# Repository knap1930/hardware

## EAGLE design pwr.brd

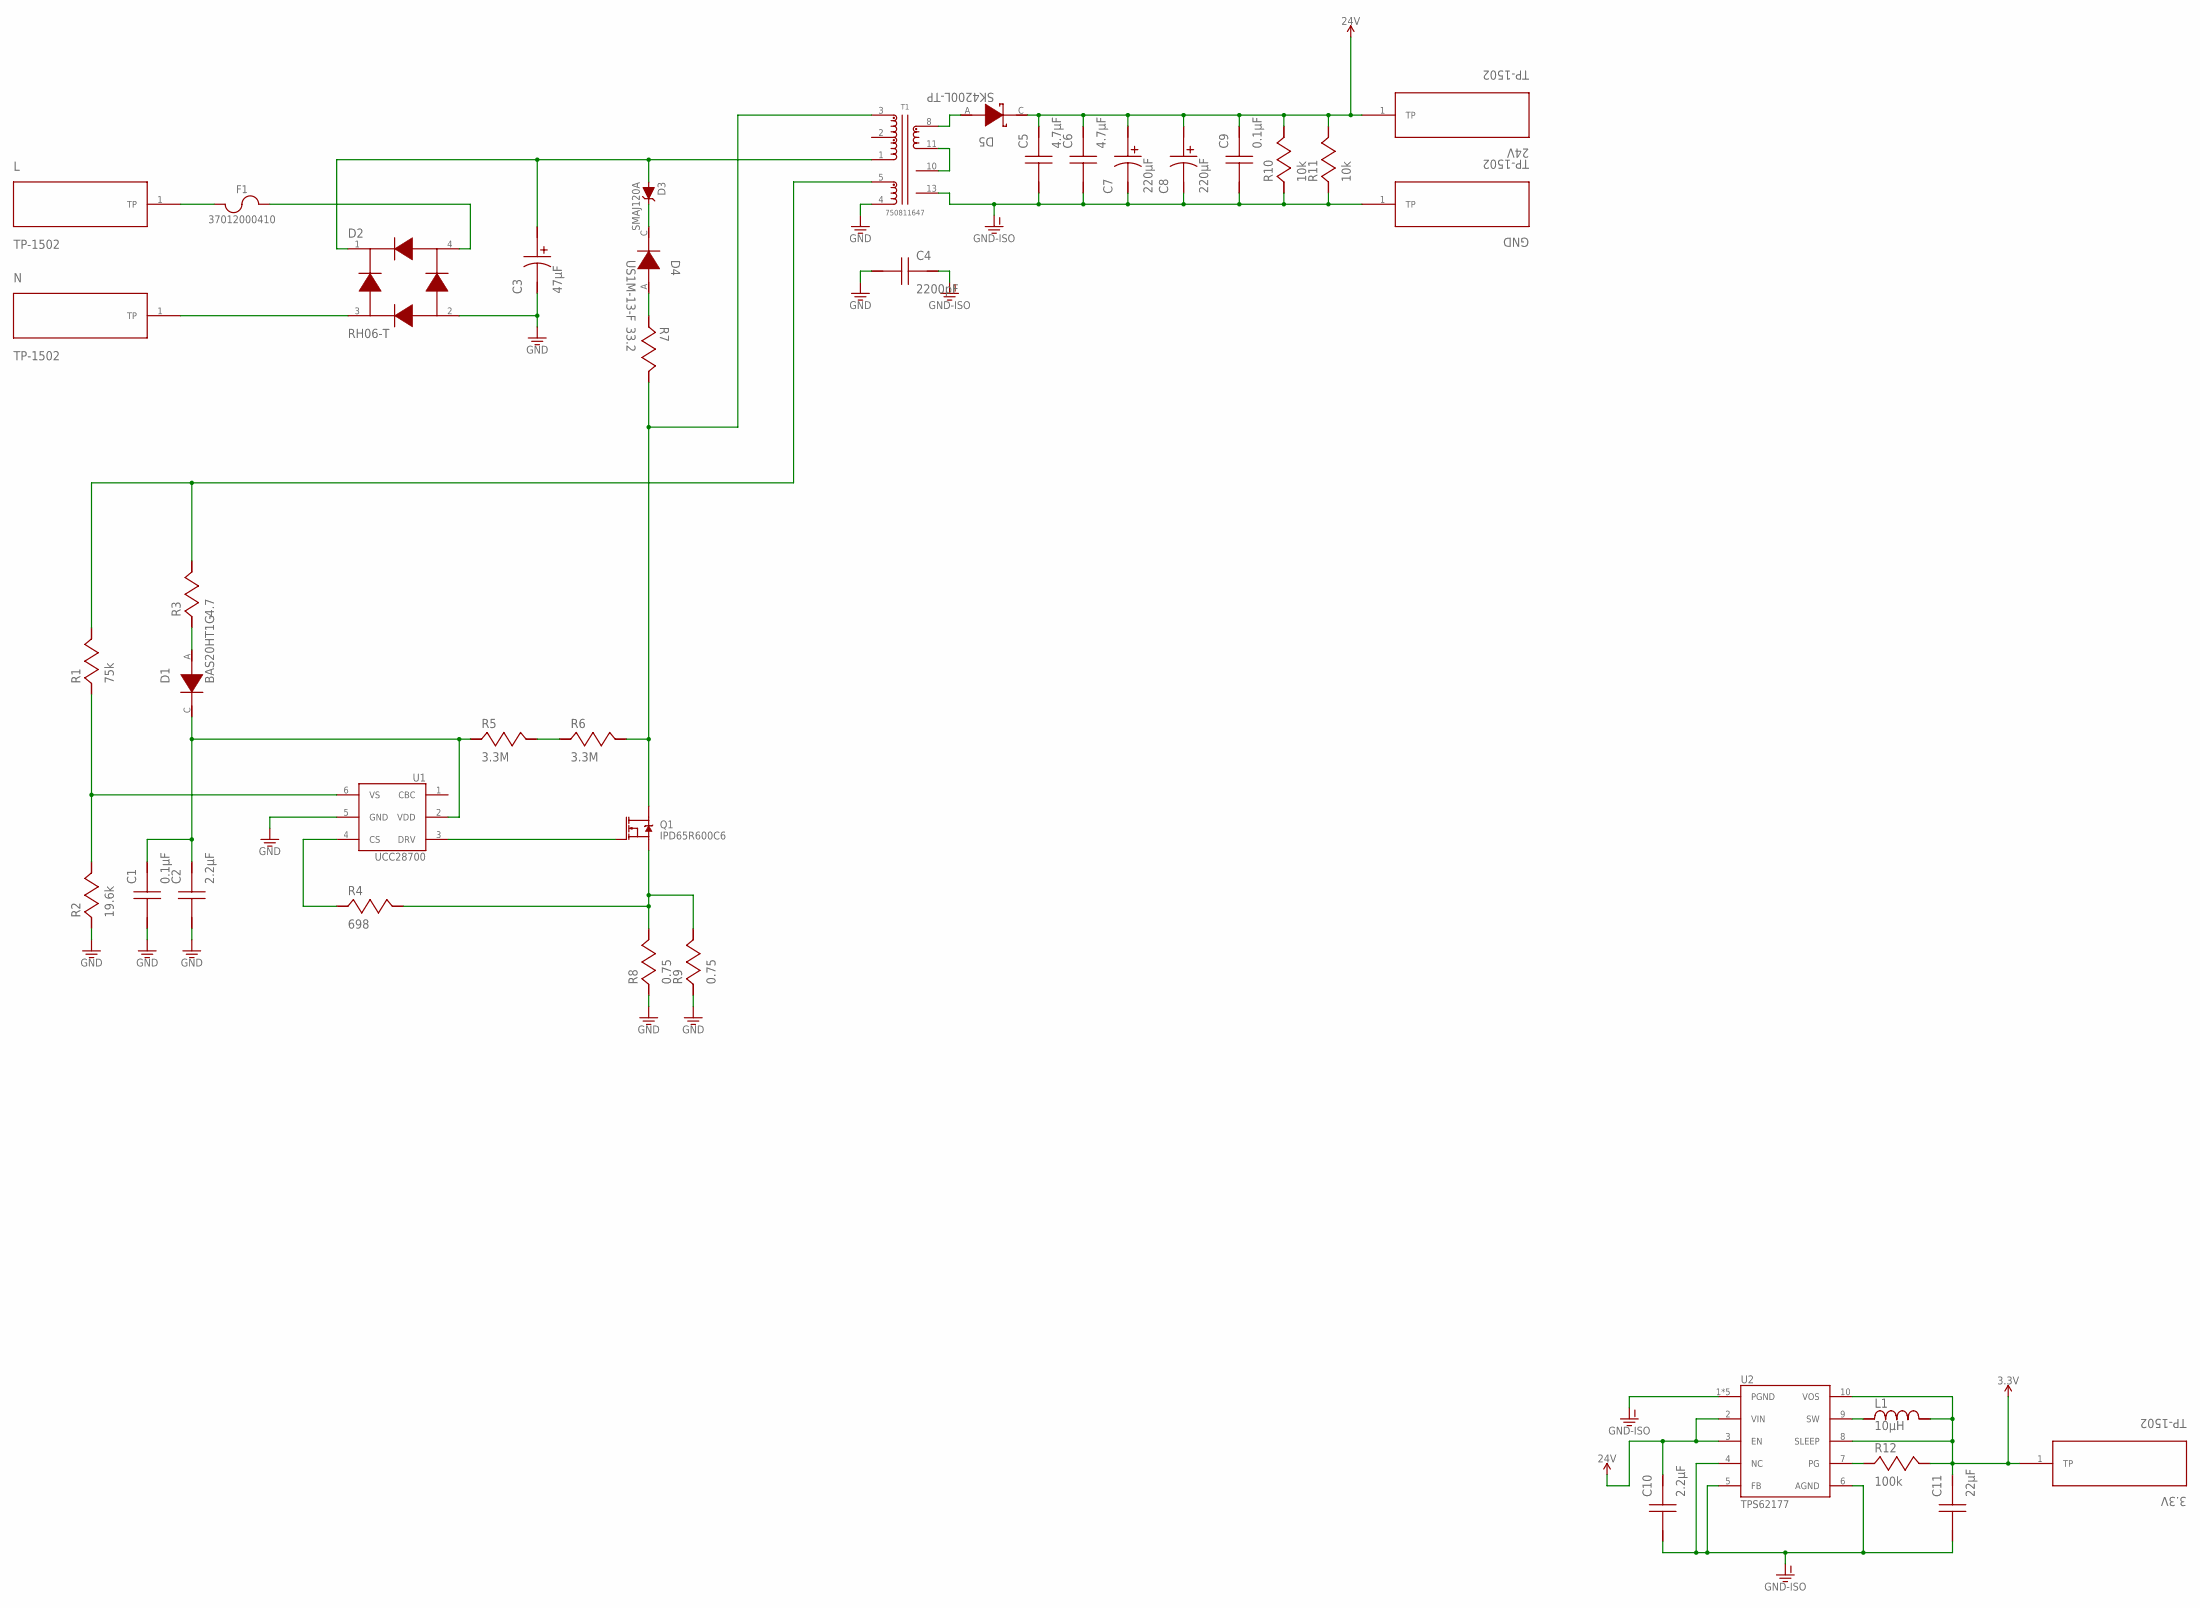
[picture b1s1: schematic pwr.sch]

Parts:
3.3V, 24V: TP-1502
C1: 0.1µF; 0603
C2: 2.2µF; 1206
C3: 47µF; CAPPR7.5-18X20
C4: 2200pF; DE1E3KX222MA4BL01
C5, C6: 4.7µF; 1206
C7, C8: 220µF; CAPPR5-10X16
C9: 0.1µF; 0805
C10: 2.2µF; 0603
C11: 22µF; 0805
D1: BAS20HT1G; SOD-323
D2: RH06-T; MINIDIP
D3: SMAJ120A; SMA
D4: US1M-13-F; SMA
D5: SK4200L-TP; SMC
F1: 37012000410; TR5_FUSE_8.5
GND: TP-1502
L: TP-1502
L1: 10µH; SDR0503
N: TP-1502
Q1: IPD65R600C6; TO-252
R1: 75k; 0603
R2: 19.6k; 0603
R3: 4.7; 1206
R4: 698; 1206
R5, R6: 3.3M; 0805
R7: 33.2; 1210
R8, R9: 0.75; 1206
R10, R11: 10k; 1206
R12: 100k; 0402
T1: 750811647
U1: UCC28700; SOT-23(6)
U2: TPS62177; P-WSON(10)

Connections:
3.3V: 3.3V.1, C11.1, L1.2, R12.1, U2.8 (SLEEP), U2.10 (VOS)
24V: 24V.1, C5.1, C6.1, C7.P$1 (1), C8.P$1 (1), C9.1, C10.1, D5.C, R10.1, R11.1, U2.2 (VIN), U2.3 (EN)
GND: C1.2, C2.2, C3.P$2 (2), C4.2, D2.2, R2.2, R8.2, R9.2, T1.4, U1.5 (GND)
GND-ISO: C4.1, C5.2, C6.2, C7.P$2 (2), C8.P$2 (2), C9.2, C10.2, C11.2, GND.1, R10.2, R11.2, T1.13, U2.1 (PGND), U2.4 (NC), U2.5 (FB), U2.6 (AGND), U2.GND, U2.P$1 (PGND), U2.P$2 (PGND), U2.P$10 (PGND)
unnamed: D2.4, F1.2
unnamed: D2.3, N.1
unnamed: C3.P$1 (1), D2.1, D3.A, T1.1
unnamed: R12.2, U2.7 (PG)
unnamed: L1.1, U2.9 (SW)
unnamed: D5.A, T1.8
unnamed: T1.10, T1.11
unnamed: D3.C, D4.C
unnamed: D4.A, R7.2
unnamed: Q1.2 (D), R6.1, R7.1, T1.3
unnamed: F1.1, L.1
unnamed: Q1.1 (G), U1.3 (DRV)
unnamed: C1.1, C2.1, D1.C, R5.2, U1.2 (VDD)
unnamed: Q1.3 (S), R4.1, R8.1, R9.1
unnamed: D1.A, R3.2
unnamed: R1.1, R3.1, T1.5
unnamed: R4.2, U1.4 (CS)
unnamed: R5.1, R6.2
unnamed: R1.2, R2.1, U1.6 (VS)

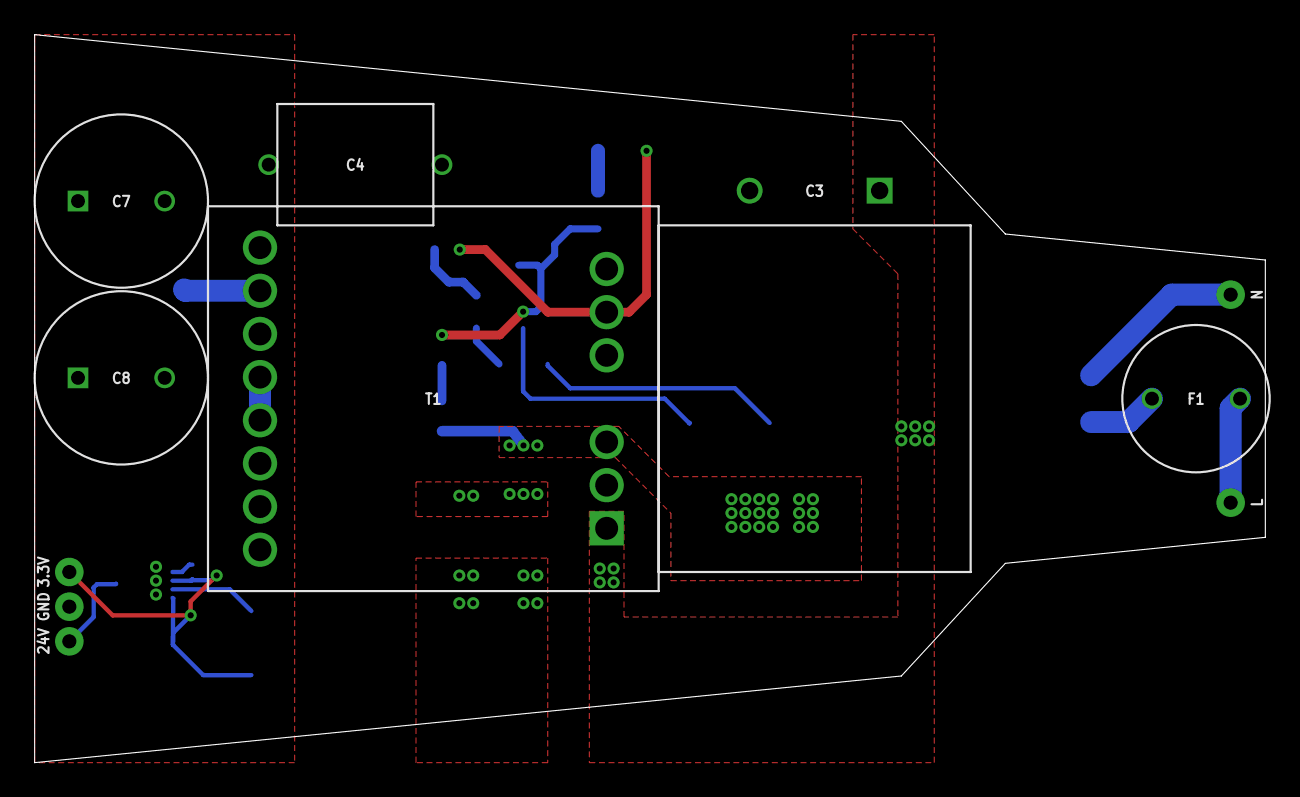
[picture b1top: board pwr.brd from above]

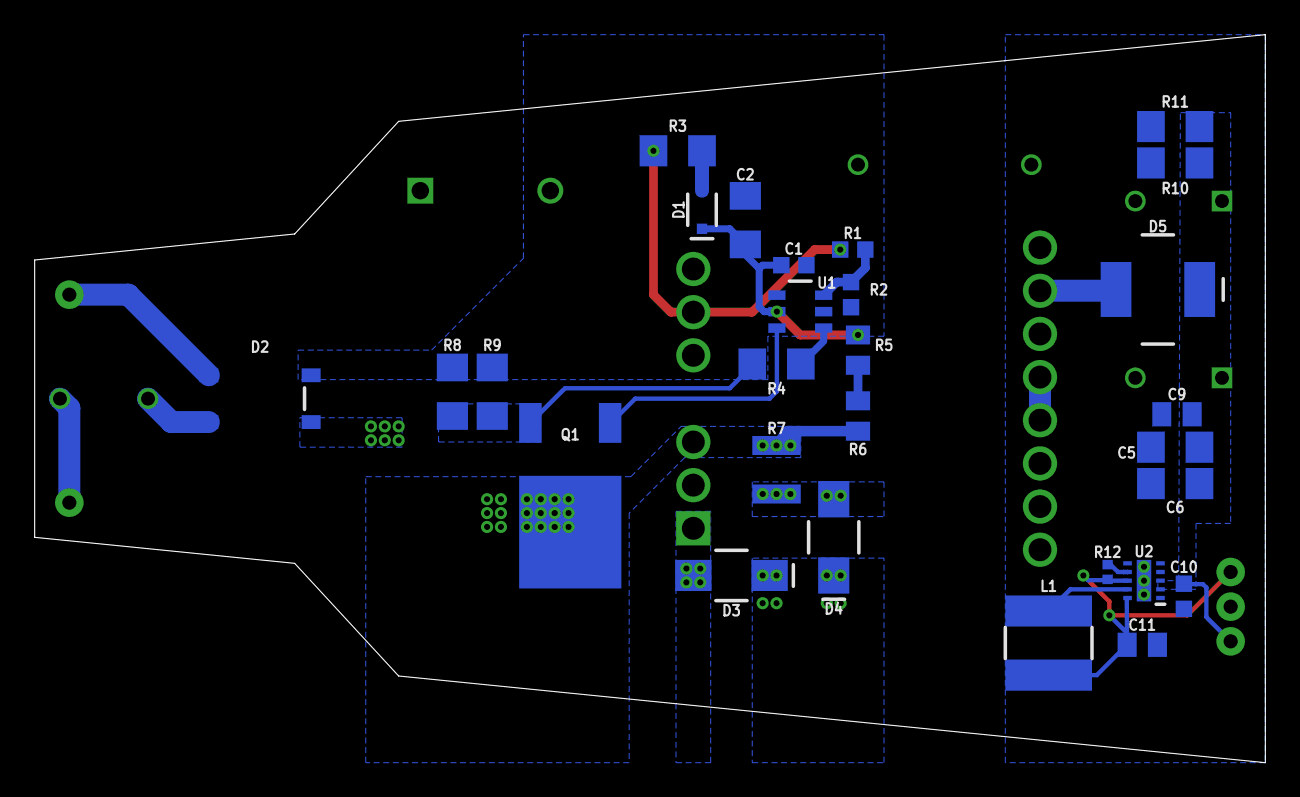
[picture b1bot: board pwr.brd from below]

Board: 2 copper layers, 71.0 x 42.0 mm, 39 parts (28 on the bottom side), 23 nets.

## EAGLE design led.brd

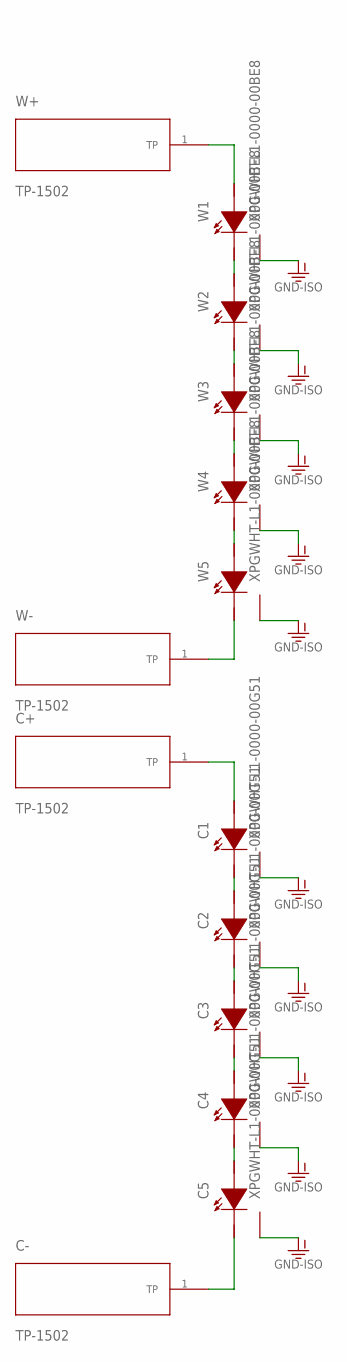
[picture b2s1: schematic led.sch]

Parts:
C1, C2, C3, C4, C5: XPGWHT-L1-0000-00G51; XLAMP-XPG
C+: TP-1502
C-: TP-1502
W1, W2, W3, W4, W5: XPGWHT-L1-0000-00BE8; XLAMP-XPG
W+: TP-1502
W-: TP-1502

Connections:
GND-ISO: C1.GND, C1.P$1 (GND), C1.P$2 (GND), C1.P$3 (GND), C2.GND, C2.P$1 (GND), C2.P$2 (GND), C2.P$3 (GND), C3.GND, C3.P$1 (GND), C3.P$2 (GND), C3.P$3 (GND), C4.GND, C4.P$1 (GND), C4.P$2 (GND), C4.P$3 (GND), C5.GND, C5.P$1 (GND), C5.P$2 (GND), C5.P$3 (GND), W1.GND, W1.P$1 (GND), W1.P$2 (GND), W1.P$3 (GND), W2.GND, W2.P$1 (GND), W2.P$2 (GND), W2.P$3 (GND), W3.GND, W3.P$1 (GND), W3.P$2 (GND), W3.P$3 (GND), W4.GND, W4.P$1 (GND), W4.P$2 (GND), W4.P$3 (GND), W5.GND, W5.P$1 (GND), W5.P$2 (GND), W5.P$3 (GND)
unnamed: C2.C, C3.A
unnamed: C1.C, C2.A
unnamed: C1.A, C+.1
unnamed: C5.C, C-.1
unnamed: W4.C, W5.A
unnamed: W1.C, W2.A
unnamed: W2.C, W3.A
unnamed: W3.C, W4.A
unnamed: C3.C, C4.A
unnamed: C4.C, C5.A
unnamed: W1.A, W+.1
unnamed: W5.C, W-.1

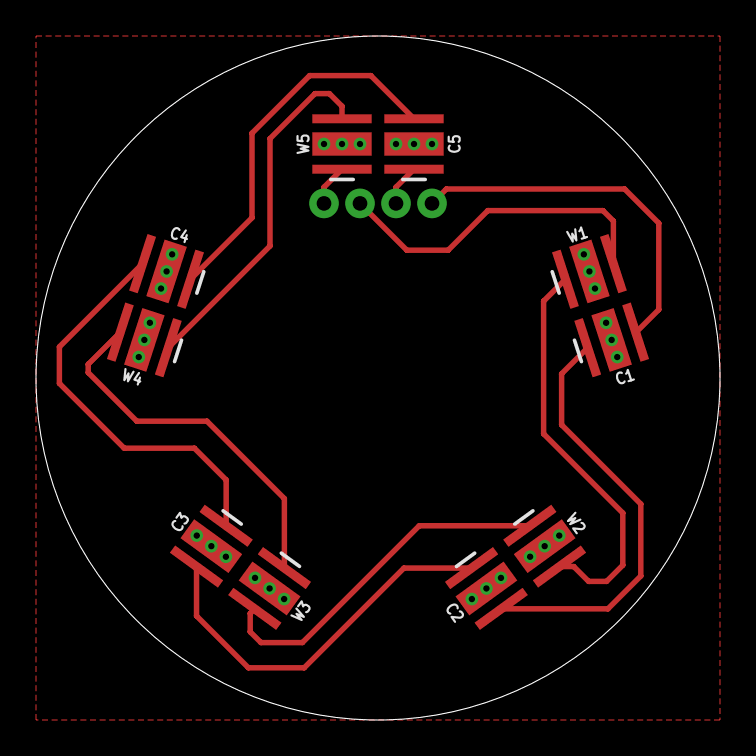
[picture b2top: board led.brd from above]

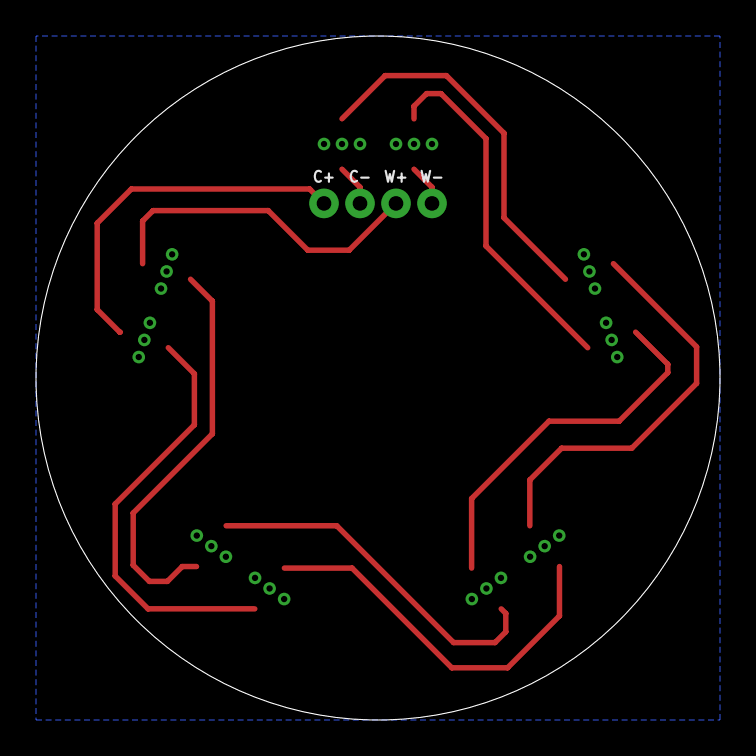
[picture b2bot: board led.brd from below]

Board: 2 copper layers, 38.0 x 38.0 mm, 14 parts (4 on the bottom side), 13 nets.

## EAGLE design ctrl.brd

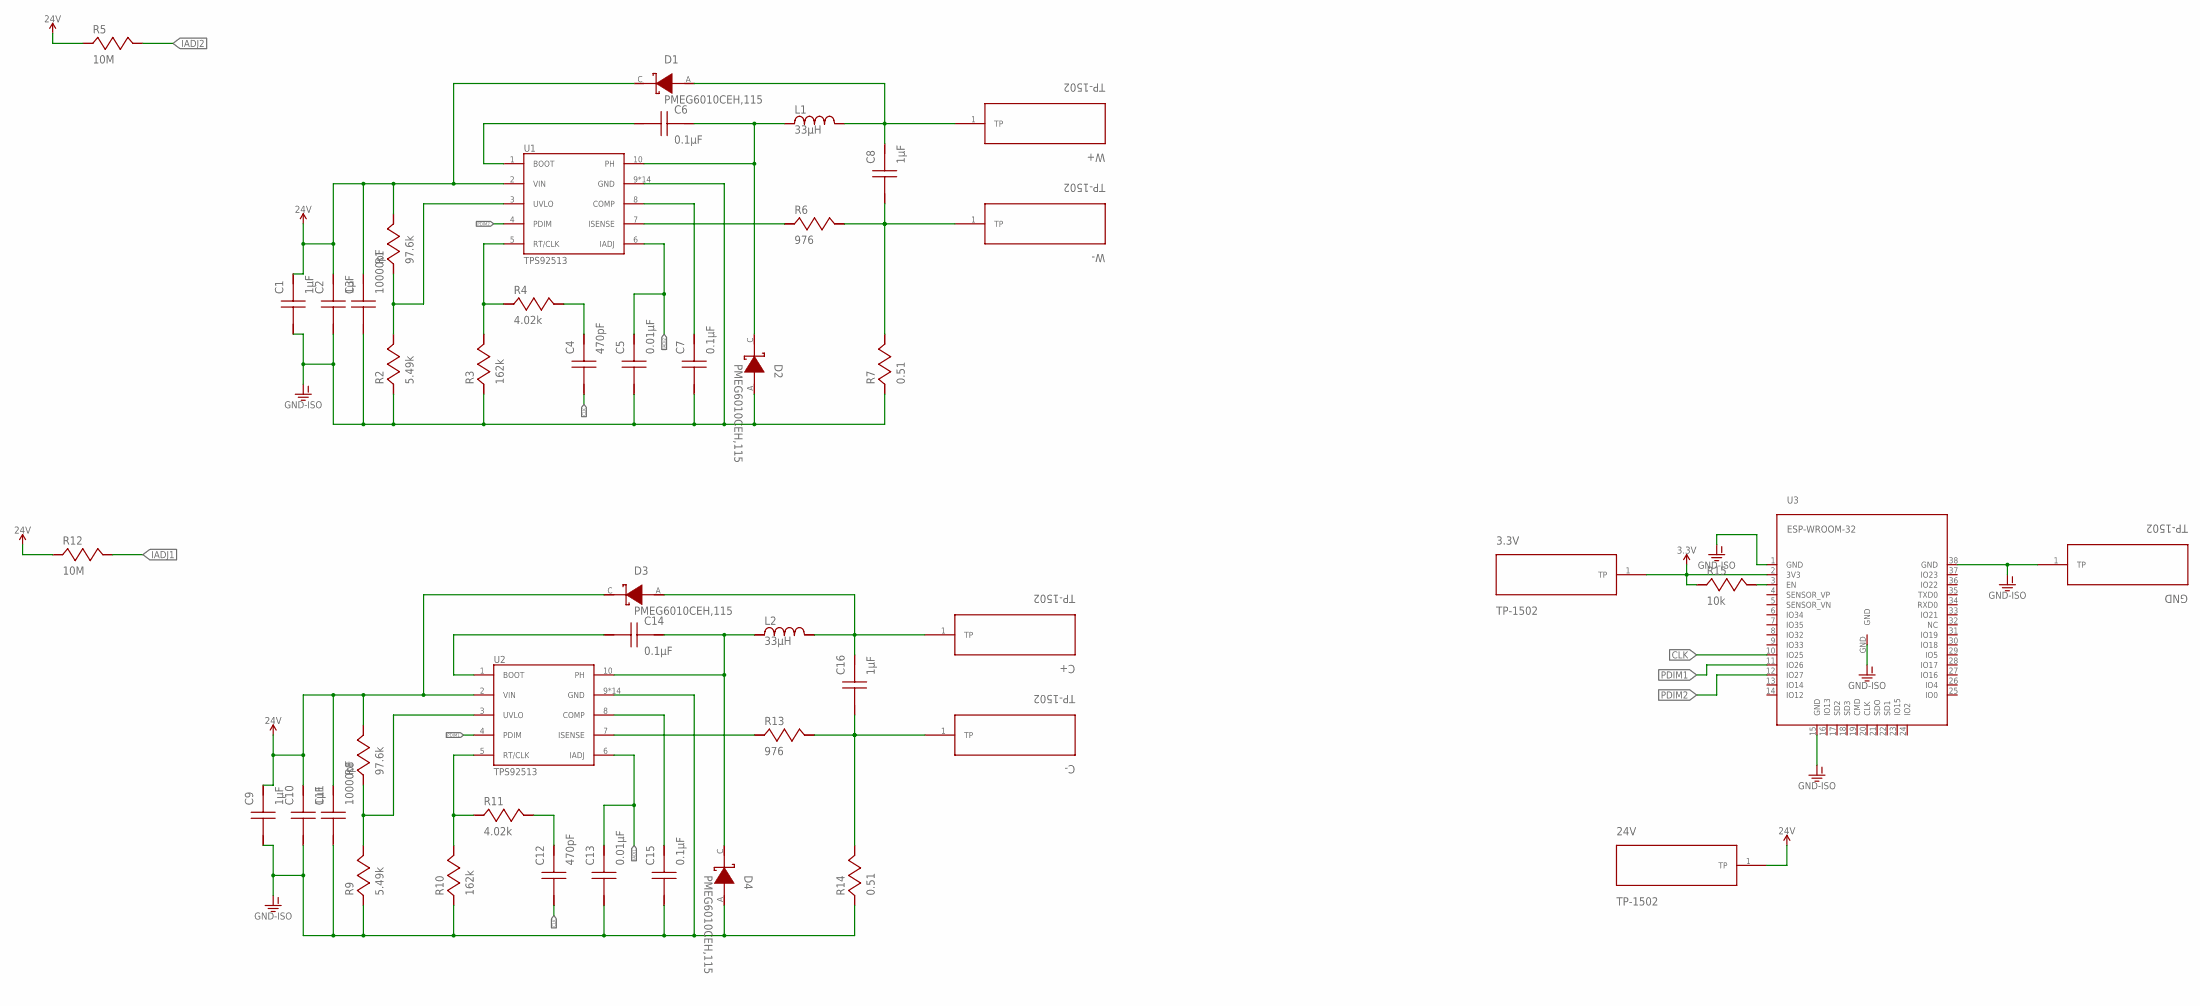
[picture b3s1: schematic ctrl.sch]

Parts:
3.3V, 24V: TP-1502
C1, C2, C9, C10: 1µF; 1206
C3, C11: 10000pF; 0402
C4, C12: 470pF; 0603
C5, C13: 0.01μF; 0805
C6, C14: 0.1µF; 0603
C7, C15: 0.1µF; 0805
C8, C16: 1µF; 0805
C+: TP-1502
C-: TP-1502
D1, D2, D3, D4: PMEG6010CEH,115; SOD-123F
GND: TP-1502
L1, L2: 33µH; SRN6045
R1, R8: 97.6k; 0402
R2, R9: 5.49k; 0402
R3, R10: 162k; 0402
R4, R11: 4.02k; 0603
R5, R12: 10M; 0402
R6, R13: 976; 0402
R7, R14: 0.51; 0805
R15: 10k; 0603
U1, U2: TPS92513
U3: ESP-WROOM-32
W+: TP-1502
W-: TP-1502

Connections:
3.3V: 3.3V.1, R15.2, U3.2 (3V3)
24V: 24V.1, C1.1, C2.1, C3.1, C9.1, C10.1, C11.1, D1.C, D3.C, R1.1, R5.2, R8.1, R12.2, U1.2 (VIN), U2.2 (VIN)
CLK: C4.2, C12.2, U3.10 (IO25)
GND-ISO: C1.2, C2.2, C3.2, C5.2, C7.2, C9.2, C10.2, C11.2, C13.2, C15.2, D2.A, D4.A, GND.1, R2.2, R3.2, R7.2, R9.2, R10.2, R14.2, U1.9 (GND), U1.GND-ISO (GND), U1.P$1 (GND), U1.P$2 (GND), U1.P$3 (GND), U1.P$4 (GND), U1.P$5 (GND), U1.P$6 (GND), U1.P$7 (GND), U1.P$8 (GND), U1.P$9 (GND), U1.P$10 (GND), U1.P$11 (GND), U1.P$12 (GND), U2.9 (GND), U2.GND-ISO (GND), U2.P$1 (GND), U2.P$2 (GND), U2.P$3 (GND), U2.P$4 (GND), U2.P$5 (GND), U2.P$6 (GND), U2.P$7 (GND), U2.P$8 (GND), U2.P$9 (GND), U2.P$10 (GND), U2.P$11 (GND), U2.P$12 (GND), U3.1 (GND), U3.15 (GND), U3.38 (GND), U3.GND
IADJ1: C13.1, R12.1, U2.6 (IADJ)
IADJ2: C5.1, R5.1, U1.6 (IADJ)
unnamed: R1.2, R2.1, U1.3 (UVLO)
unnamed: R8.2, R9.1, U2.3 (UVLO)
unnamed: C14.1, D4.C, L2.1, U2.10 (PH)
unnamed: R10.1, R11.2, U2.5 (RT/CLK)
unnamed: C15.1, U2.8 (COMP)
unnamed: C14.2, U2.1 (BOOT)
unnamed: R13.2, U2.7 (ISENSE)
unnamed: C12.1, R11.1
unnamed: C16.1, C+.1, D3.A, L2.2
unnamed: C16.2, C-.1, R13.1, R14.1
unnamed: C6.1, D2.C, L1.1, U1.10 (PH)
unnamed: R3.1, R4.2, U1.5 (RT/CLK)
unnamed: C7.1, U1.8 (COMP)
unnamed: C6.2, U1.1 (BOOT)
unnamed: R6.2, U1.7 (ISENSE)
unnamed: C8.1, D1.A, L1.2, W+.1
unnamed: C4.1, R4.1
unnamed: C8.2, R6.1, R7.1, W-.1
unnamed: R15.1, U3.3 (EN)
PDIM1: U2.4 (PDIM), U3.11 (IO26)
PDIM2: U1.4 (PDIM), U3.12 (IO27)

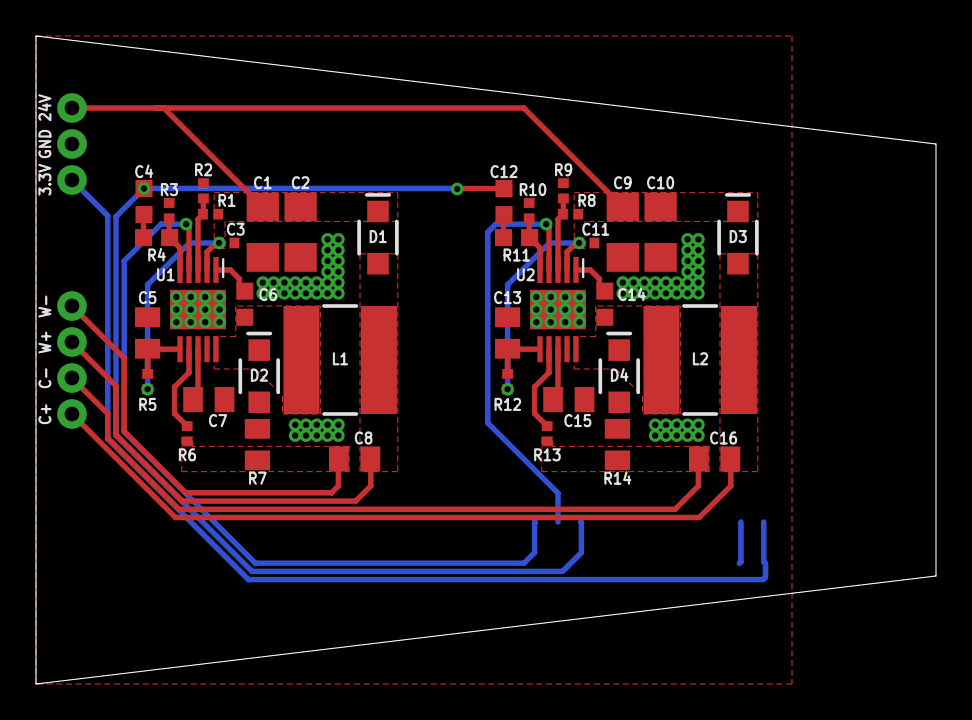
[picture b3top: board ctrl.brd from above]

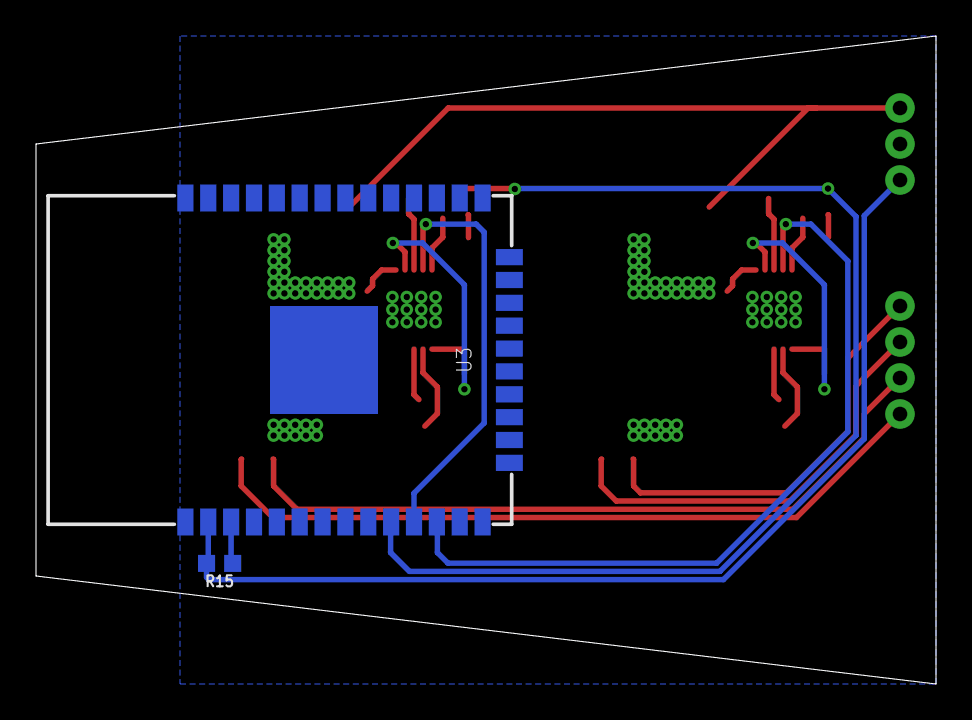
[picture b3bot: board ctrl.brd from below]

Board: 2 copper layers, 50.0 x 36.0 mm, 47 parts (2 on the bottom side), 27 nets.

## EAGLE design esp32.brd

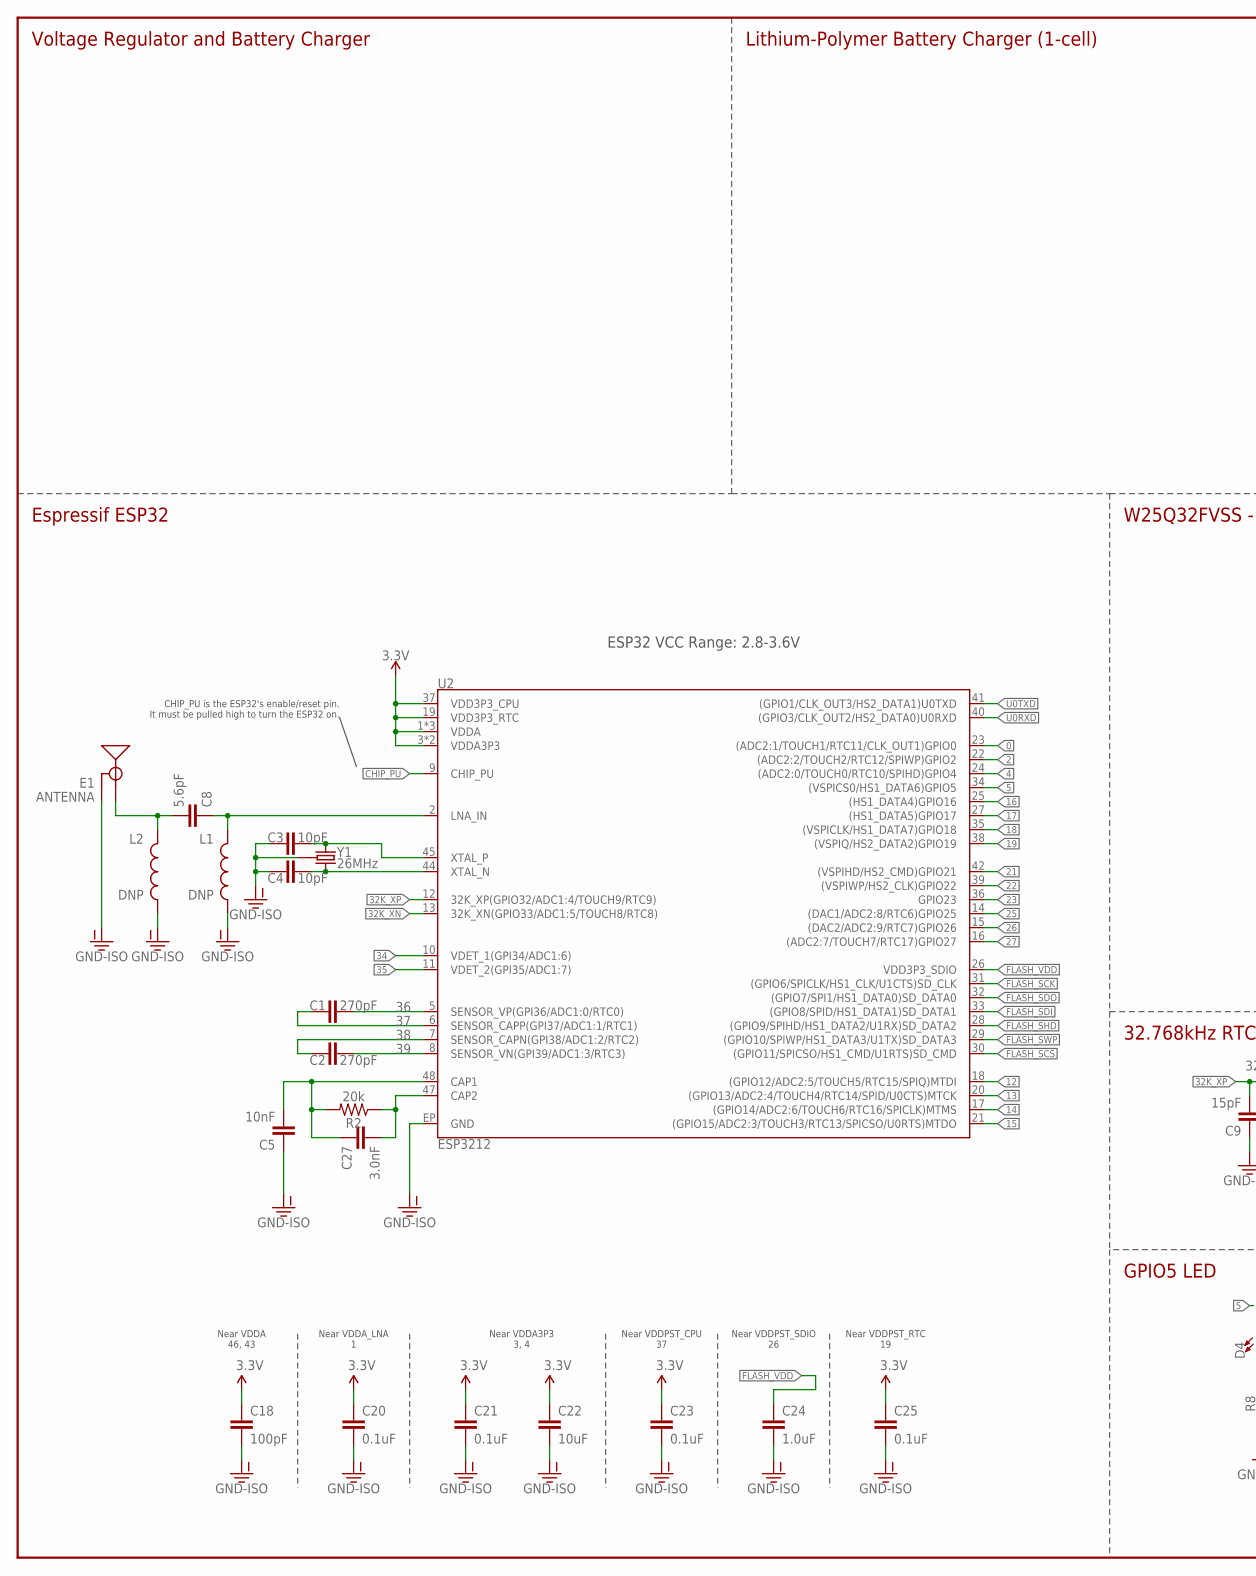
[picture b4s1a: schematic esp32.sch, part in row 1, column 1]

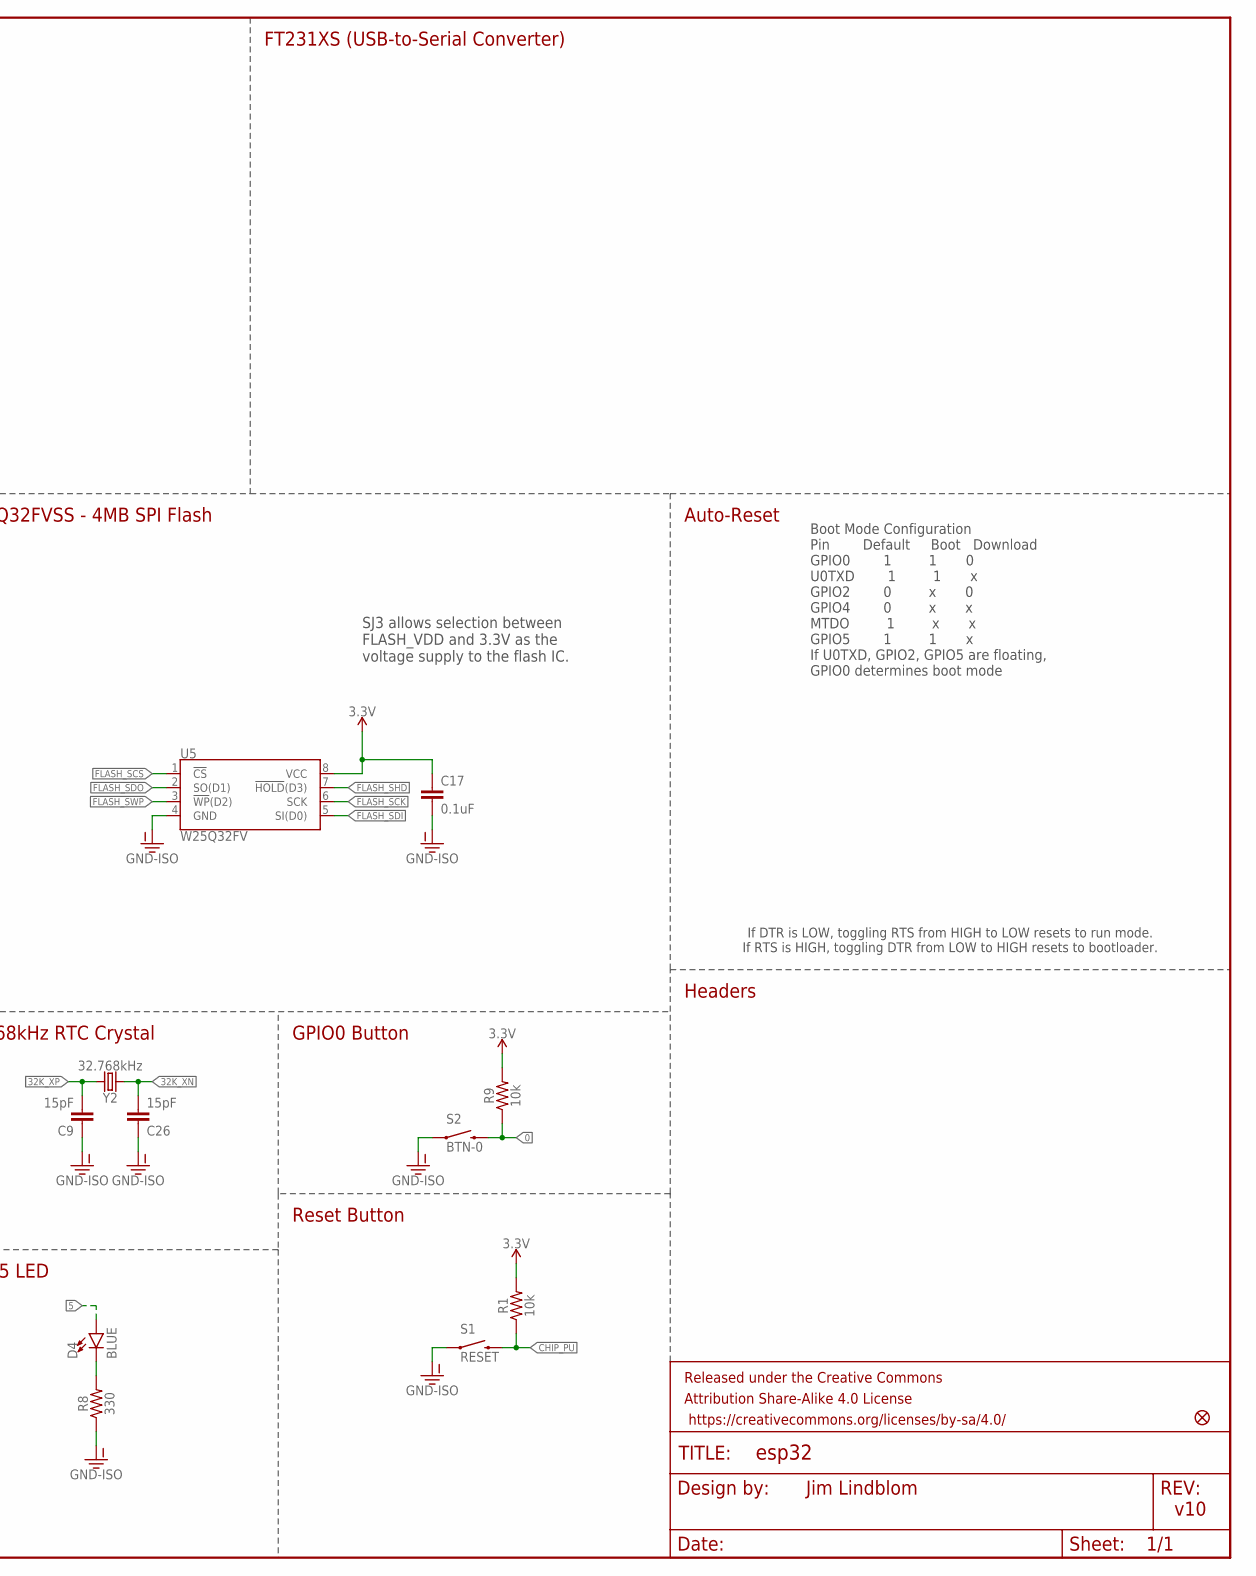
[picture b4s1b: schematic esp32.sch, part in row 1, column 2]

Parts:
C1, C2: 270pF; 0603
C3, C4: 10pF; 0603
C5: 10nF; 0603
C8: 5.6pF; 0603
C9, C26: 15pF; 0603
C17, C20, C21, C23, C25: 0.1uF; 0603
C18: 100pF; 0603
C22: 10uF; 0603
C24: 1.0uF; 0603
C27: 3.0nF; 0603
D4: BLUE; LED-0603
E1: ANTENNA; TRACE_ANTENNA_2.4GHZ_25.7MM_TUNED
FD2: FIDUCIALUFIDUCIAL; MICRO-FIDUCIAL
FRAME1: FRAME-LEDGER; CREATIVE_COMMONS
L1, L2: DNP; 0603
R1, R9: 10k; 0603
R2: 20k; 0603
R8: 330; 0603
S1: RESET; TACTILE_SWITCH_SMD_4.6X2.8MM
S2: BTN-0; TACTILE_SWITCH_SMD_4.6X2.8MM
U2: ESP3212; QFN48-0.4MM
U5: W25Q32FV; SOIC-8
Y1: 26MHz; CRYSTAL-SMD-3.2X2.5
Y2: 32.768kHz; CRYSTAL-SMD-3.2X1.5MM

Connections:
0: R9.1, S2.3 (2), S2.4 (2), U2.23 ((ADC2:1/TOUCH1/RTC11/CLK_OUT1)GPIO0)
2: U2.22 ((ADC2:2/TOUCH2/RTC12/SPIWP)GPIO2)
3.3V: C17.1, C18.1, C20.1, C21.1, C22.1, C23.1, C25.1, R1.2, R9.2, U2.1 (VDDA), U2.3 (VDDA3P3), U2.4 (VDDA3P3), U2.19 (VDD3P3_RTC), U2.37 (VDD3P3_CPU), U2.43 (VDDA), U2.46 (VDDA), U5.8 (VCC)
4: U2.24 ((ADC2:0/TOUCH0/RTC10/SPIHD)GPIO4)
5: D4.A, U2.34 ((VSPICS0/HS1_DATA6)GPIO5)
12: U2.18 ((GPIO12/ADC2:5/TOUCH5/RTC15/SPIQ)MTDI)
13: U2.20 ((GPIO13/ADC2:4/TOUCH4/RTC14/SPID/U0CTS)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)
14: U2.17 ((GPIO14/ADC2:6/TOUCH6/RTC16/SPICLK)MTMS)
15: U2.21 ((GPIO15/ADC2:3/TOUCH3/RTC13/SPICSO/U0RT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)
16: U2.25 ((HS1_DATA4)GPIO16)
17: U2.27 ((HS1_DATA5)GPIO17)
18: U2.35 ((VSPICLK/HS1_DATA7)GPIO18)
19: U2.38 ((VSPIQ/HS2_DATA2)GPIO19)
21: U2.42 ((VSPIHD/HS2_CMD)GPIO21)
22: U2.39 ((VSPIWP/HS2_CLK)GPIO22)
23: U2.36 (GPIO23)
25: U2.14 ((DAC1/ADC2:8/RTC6)GPIO25)
26: U2.15 ((DAC2/ADC2:9/RTC7)GPIO26)
27: U2.16 ((ADC2:7/TOUCH7/RTC17)GPIO27)
32K_XN: C26.2, U2.13 (32K_XN(GPIO33/ADC1:5/TOUCH8/RTC8)), Y2.P$2 (2)
32K_XP: C9.2, U2.12 (32K_XP(GPIO32/ADC1:4/TOUCH9/RTC9)), Y2.P$1 (1)
34: U2.10 (VDET_1(GPI34/ADC1:6))
35: U2.11 (VDET_2(GPI35/ADC1:7))
36: C1.2, U2.5 (SENSOR_VP(GPI36/ADC1:0/RTC0))
37: C1.1, U2.6 (SENSOR_CAPP(GPI37/ADC1:1/RTC1))
38: C2.1, U2.7 (SENSOR_CAPN(GPI38/ADC1:2/RTC2))
39: C2.2, U2.8 (SENSOR_VN(GPI39/ADC1:3/RTC3))
CAP_10N: C5.2, C27.1, R2.2, U2.48 (CAP1)
CHIP_PU: R1.1, S1.3 (2), S1.4 (2), U2.9 (CHIP_PU)
FLASH_SCK: U2.31 ((GPIO6/SPICLK/HS1_CLK/U1CTS)SD_CLK), U5.6 (SCK)
FLASH_SCS: U2.30 ((GPIO11/SPICSO/HS1_CMD/U1RTS)SD_CMD), U5.1 (!CS!)
FLASH_SDI: U2.33 ((GPIO8/SPID/HS1_DATA1)SD_DATA1), U5.5 (SI(D0))
FLASH_SDO: U2.32 ((GPIO7/SPI1/HS1_DATA0)SD_DATA0), U5.2 (SO(D1))
FLASH_SHD: U2.28 ((GPIO9/SPIHD/HS1_DATA2/U1RX)SD_DATA2), U5.7 (!HOLD!(D3))
FLASH_SWP: U2.29 ((GPIO10/SPIWP/HS1_DATA3/U1TX)SD_DATA3), U5.3 (!WP!(D2))
FLASH_VDD: C24.1, U2.26 (VDD3P3_SDIO)
GND: C3.1, C4.1, C5.1, C9.1, C17.2, C18.2, C20.2, C21.2, C22.2, C23.2, C24.2, C25.2, C26.1, E1.GND, E1.GND2 (GND), L1.2, L2.2, R8.1, S1.1, S1.2 (1), S2.1, S2.2 (1), U2.EP (GND), U5.4 (GND), Y1.2 (GND), Y1.4 (GND)
LNA_IN: C8.1, L1.1, U2.2 (LNA_IN)
unnamed: D4.C, R8.2
unnamed: C27.2, R2.1, U2.47 (CAP2)
unnamed: C3.2, U2.45 (XTAL_P), Y1.1
unnamed: C4.2, U2.44 (XTAL_N), Y1.3 (2)
TRACE_ANT: C8.2, E1.ANT (SIGNAL), L2.1
U0RXD: U2.40 ((GPIO3/CLK_OUT2/HS2_DATA0)U0RXD)
U0TXD: U2.41 ((GPIO1/CLK_OUT3/HS2_DATA1)U0TXD)

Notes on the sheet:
Boot Mode Configuration Pin Default Boot Download GPIO0 1 1 0 U0TXD 1 1 x GPIO2 0 x 0 GPIO4 0 x x MTDO 1 x x GPIO5 1 1 x If U0TXD, GPIO2, GPIO5 are floating, GPIO0 determines boot mode
FT231XS (USB-to-Serial Converter)
Voltage Regulator and Battery Charger
Lithium-Polymer Battery Charger (1-cell)
Auto-Reset
Near VDDA 46, 43
Near VDDA_LNA 1
Near VDDA3P3 3, 4
Near VDDPST_CPU 37
Near VDDPST_SDIO 26
Near VDDPST_RTC 19
Espressif ESP32
W25Q32FVSS - 4MB SPI Flash
32.768kHz RTC Crystal
GPIO0 Button
Reset Button
GPIO5 LED
Headers
v10
Jim Lindblom
ESP32 VCC Range: 2.8-3.6V
SJ3 allows selection between FLASH_VDD and 3.3V as the voltage supply to the flash IC.
If DTR is LOW, toggling RTS from HIGH to LOW resets to run mode. If RTS is HIGH, toggling DTR from LOW to HIGH resets to bootloader.
CHIP_PU is the ESP32's enable/reset pin. It must be pulled high to turn the ESP32 on.

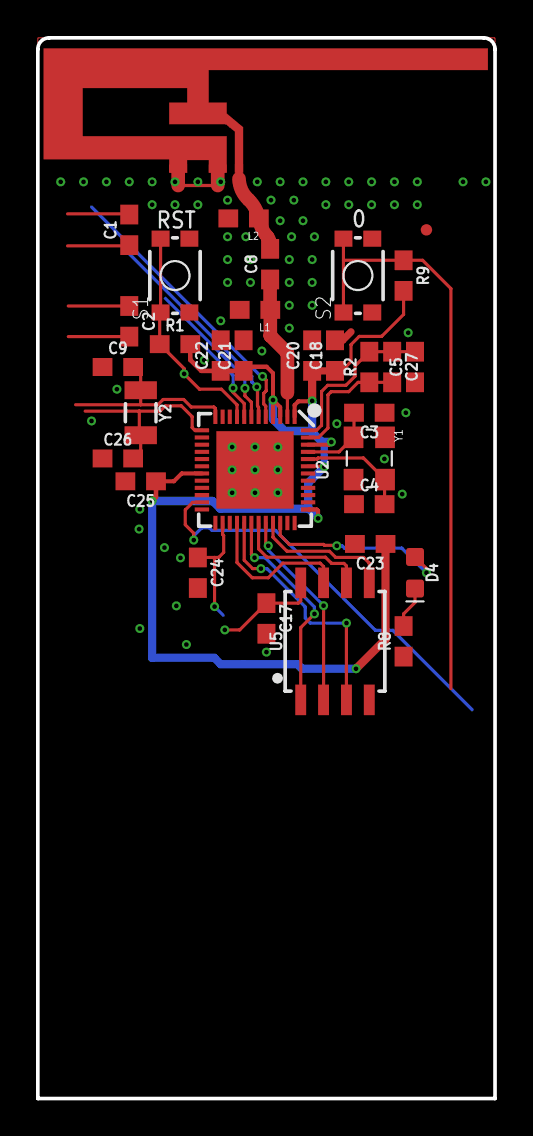
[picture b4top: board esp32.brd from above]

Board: 2 copper layers, 25.4 x 58.9 mm, 33 parts (0 on the bottom side), 25 nets.

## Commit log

2017-04-22 save
2017-04-22 ssss
2017-05-11 ordered
2017-05-13 should be good to order parts
2017-05-13 order this
2017-05-13 update lib
2017-05-14 getting close
2017-05-15 pwr to osh
2017-06-02 sent
2017-06-06 add datasheets
2017-06-17 works
2017-06-21 temp
2017-06-26 save?
2017-07-28 saveeee
2017-07-29 ignore
2017-07-29 rearrange positions
2017-08-04 use this

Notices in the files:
parts and their libraries:
SparkFun-Electromechanical: Licensing: Creative Commons ShareAlike 4.0 International - https://creativecommons.org/licenses/by-sa/4.0
SparkFun-Aesthetics: Released under the Creative Commons Attribution Share-Alike 4.0 License
SparkFun-Aesthetics: https://creativecommons.org/licenses/by-sa/4.0
